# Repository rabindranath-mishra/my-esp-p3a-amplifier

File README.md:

# My ESP P3A Amplifier Build (Y2026)

I have been making my own audio equipment since I was a teenager. I firmly believe that if you understand electronics, it is far better to build your own gear. You can craft something of exceptionally high quality, tailored precisely to your personal taste, and at a fraction of the cost of a mediocre commercial unit. For that matter, I build anything that I feel is not worth the retail price tag for its given quality—particularly in the domains of computers, electronics, and anything that can be 3D printed. Fortunately, all three are lifelong hobbies of mine.

Back in 2013–14, I built a stereo power amplifier for my home. My commercial home theater system (a mediocre setup received as a wedding gift) had given up the ghost, and repairing it was neither economical nor satisfying. I was unwilling to shell out exorbitant sums for high-end retail audio gear. After deep research across the DIY audio community, I chose to build a design by one of my greatest inspirations, Rod Elliott (Elliott Sound Products): the legendary [ESP Project 3A (P3A)](https://www.sound-au.com/project3a.htm). 

That 2013 amplifier was an absolute workhorse. It sounded magnificent and served faithfully for over a decade without missing a single beat. However, I was never 100% satisfied with the physical build. Back then in Bangalore, sourcing authentic, audiophile-grade components was an uphill battle involving difficult international orders, long customs delays, and DIY chemical etching of single-sided copper clad boards in my garage. The final unit lacked a professional finish and involved several mechanical compromises.

Fast forward to **2026**: I decided it was time to build a worthy successor. After re-evaluating modern DIY open-source topologies—from Class D modules to complex discrete designs—I reached the unmistakable conclusion that the **ESP P3A** is still King. Its Class AB topology is elegant, highly reliable, and delivers sound quality that easily rivals commercial amplifiers costing thousands of dollars. More importantly, the DIY landscape in India has completely transformed: quality passive components, genuine transistors, fast PCB fabrication (such as JLCPCB), and reputable domestic component distributors are now readily available. In 2026, I could finally build this amplifier to absolute perfection, with zero compromises.

---

## System Architecture & The 5 Building Blocks

A truly great power amplifier is not just an amplifier PCB; it is a carefully engineered system where the power supply, soft start, protection, and grounding work together in total harmony. 

This build integrates five core modules:

1. **The Amplifier Stage (ESP P3A)** – Dual-mono Class AB discrete power amplifier based on [Rod Elliott's ESP P3A](https://www.sound-au.com/project3a.htm).
2. **The Power Supply** – Ultra-low-noise linear power supply with a massive 40,000 µF reserve, inspired by Texas Instruments Reference Design [AN-1849: An Audio Amplifier Power Supply Design](https://www.ti.com/lit/an/snaa057c/snaa057c.pdf).
3. **The Soft Start Circuit** – Mains inrush limiter with auxiliary DC power, inspired by [ESP Project 39](https://www.sound-au.com/project39.htm).
4. **Speaker Protection & Fast Muting (ESP P33)** – DC offset sensing, turn-on delay, and instantaneous AC-loss drop-out based on [ESP Project 33](https://www.sound-au.com/project33.htm).
5. **The Ground Loop Breaker** – Safety earthing and hum-elimination network based on [Rod Elliott's Earthing Guide](https://www.sound-au.com/earthing.htm).

While planning the PCB layouts, I discovered that [gabriel-gearip](https://github.com/gabriel-gearip) had already produced clean, modular KiCad PCB layouts for both the P3A amplifier and P33 speaker protection boards. Check out his [GitHub repository](https://github.com/gabriel-gearip/p3a-amplifier). I chose to use his Gerber files directly for the P3A and P33 boards. For the **Power Supply** and **Soft Start**, I custom-designed the PCBs in KiCad to fit my chassis layout and ordered them fabricated via JLCPCB. Most components were procured domestically from [Robu.in](https://robu.in) and [Sharvi Electronics](https://sharvielectronics.com), along with trusted specialty suppliers.

---

## 1. The Amplifier: ESP P3A

### The Topology
Rod Elliott's Project 3A is celebrated worldwide for good reason. It is a symmetrical-input, discrete Class AB power amplifier that avoids unnecessary complexity while delivering pristine linearity, wide bandwidth, and unconditional stability into real-world loudspeaker loads.

* **Input Stage**: A balanced differential pair (long-tailed pair) utilizing low-noise **BC546** NPN transistors (Q1, Q2) with emitter degeneration resistors ($1\text{ k}\Omega$). This maximizes open-loop linearity and slew rate while minimizing DC offset.
* **Voltage Amplification Stage (VAS)**: A high-current Class A VAS driven by a **BD140** (Q4). 
* **Bias Servo ($V_{be}$ Multiplier)**: Implemented with **Q9 (BC546)**. Because the P3A uses a **Compound Feedback Pair (CFP / Sziklai pair)** output stage, thermal stability is dictated by the driver transistors rather than the output power transistors. Accordingly, Q9 is thermally coupled directly to driver transistor **Q6 (BD140)**—tied face-to-face with thermal paste—rather than mounted on the main heatsink. Quiescent current adjustment is calibrated via a high-precision **Bourns 3296W** multi-turn potentiometer (RV1).
* **Driver & Output Stage**: High-speed **BD139/BD140** drivers feed a complementary pair of modern high-power audio transistors: the **NJW0281** (NPN) and **NJW0302** (PNP) in rugged TO-3P packages. Rated at 15 A, 250 V, and 150 W with an outstanding $30\text{ MHz}$ gain bandwidth, these ON Semiconductor devices exhibit extraordinary $h_{FE}$ linearity across their entire current swing.
* **Emitter Resistors**: Low-inductance **Bevenbi Audio Grade 0.33 $\Omega$ / 10 W** non-inductive ceramic power resistors ensure rock-solid current sharing and thermal stability.
* **On-Board Protection & Zobel**: Independent **3 A fast-blow DC rail fuses** right on each board protect against short circuits, while an on-board Zobel network ($10\ \Omega + 100\text{ nF}$) prevents high-frequency parasitic oscillation into reactive speaker cables.

### Power Output
Operating from $\pm 35\text{ V}$ DC rails, each mono block produces:
* **~60 W RMS into 8 $\Omega$**
* **~100 W RMS into 4 $\Omega$**

This is the sweet spot for domestic high-fidelity listening, providing ample clean headroom, high damping factor, and effortless dynamics without running into thermal or transformer saturation issues.

---

## 2. The Power Supply

An audio amplifier is fundamentally an active valve that modulates raw DC from its power supply into an audio signal. If the power supply is noisy, under-capacitored, or poorly laid out, even the finest amplifier circuit will sound sluggish, hollow, and noisy.

For this build, I designed a dedicated heavy-duty dual-rail linear supply inspired by Texas Instruments' benchmark application report, [AN-1849: An Audio Amplifier Power Supply Design](https://www.ti.com/lit/an/snaa057c/snaa057c.pdf).

### Key Specifications & Design Highlights:
* **300 VA EI-Core Transformer**: Custom heavy-iron transformer with a $230\text{ V}$ AC primary and a **$25\text{--}0\text{--}25\text{ V}$ AC** center-tapped secondary. Under rectification, this produces clean $\pm 35.3\text{ V}$ DC unloaded, settling to a rock-solid $\pm 34\text{ V}$ to $\pm 35\text{ V}$ under continuous load. Mounted on rubber vibration-damping isolation mounts to eliminate mechanical hum.
* **40,000 µF Total Filter Reservoir**: Four massive **Bevenbi 10,000 µF / 100 V** high-ripple snap-in electrolytic capacitors provide **20,000 µF per rail**. This gargantuan capacitive reserve delivers instantaneous transient current for explosive bass slam and reduces 100 Hz ripple to mere millivolts.
* **KBPC3510 Bridge Rectifier — Chassis-Cooled**: Full-wave rectification is handled by a **KBPC3510** (35 A / 1000 V) bridge rectifier. Rather than mounting it upright on the PCB top with a bulky heatsink, I inverted it onto the **underside of the PCB** so that its bare metal body presses flush against the steel chassis floor. A dab of **thermal paste** between the rectifier body and the chassis floor ensures excellent thermal conduction. The chassis itself acts as a passive heatsink, keeping the PCB top uncluttered and the rectifier running cool even under sustained high-current loads.
* **Dual-Footprint High-Frequency Film Bypassing**: To filter out high-frequency noise and RF hash that large can electrolytics cannot absorb due to internal equivalent series inductance (ESL), premium film capacitors bypass each rail.
* **Diode Snubbers & Safety Bleeders**: High-voltage film snubber capacitors across the bridge rectifier legs suppress diode reverse-recovery ringing, while bleeder resistors safely drain the 40,000 µF filter bank when mains power is switched off.
* **Star Grounding Bus**: Thick, high-current copper star ground traces on the PCB provide clean, low-impedance ground return paths for both amplifier channels, the speaker ground terminals, and the center tap.

*(Need this custom PCB? email me at `rabindranathm@gmail.com`.)*

---

## 3. The Soft Start Circuit

### The Problem
A 300 VA linear transformer coupled with a discharged 40,000 µF capacitor bank represents a dead short circuit at the split-second of turn-on. The instantaneous inrush current can spike to **30 to 50+ Amperes**, which routinely trips household miniature circuit breakers (MCBs), stresses or pits the mains power switch, and degrades rectifier diodes over time.

### The Solution: ESP Project 39 Architecture
Inspired by [ESP Project 39](https://www.sound-au.com/project39.htm), I designed a self-contained soft-start PCB that safely limits inrush current while adding isolated auxiliary power rails.

1. **Inrush Current Limiting**: Three heavy-duty **NTC thermistors** (TH1, TH2, TH3) are placed in series with the AC mains live feed. In their cold state, their combined resistance safely chokes the turn-on inrush current to a gentle few amperes.
2. **Precision Delay & Bypass**: An onboard isolated switch-mode power module (**EASY POWER SO12V51000**, accepting $110\text{--}260\text{ V}$ AC and outputting dual isolated $+12\text{ V}$ and $+5\text{ V}$ DC at 1 A) powers an RC timing circuit. After a controlled delay of approximately **100 to 300 mill seconds** (adjustable via an onboard 100 k $\Omega$ trimpot), transistor Q1 turns on and energizes a heavy-duty **SUN HOLD RAS-1215 15 A relay**. The relay contacts short out the NTC thermistors, delivering 100% unimpeded AC mains to the main transformer.
3. **Auxiliary Dual DC Power (+12V & +5V)**: Generating isolated low-voltage DC directly on the soft-start board provides two versatile auxiliary rails:
   * **$+12\text{ V}$ DC**: Powers the **dual chassis exhaust fans** and the **illuminated front-panel power switch LED halo ring**, keeping fan motor commutation hash completely isolated from the sensitive audio rails.
   * **$+5\text{ V}$ DC**: A dedicated clean 5V rail that can be used to power internal or add-on **Bluetooth audio receiver modules** (such as CSR8675, PCM5102, or QCC series boards) or USB DACs without requiring an extra wall wart or inducing digital ground hum into the analog signal path!

*(Need this custom PCB? email me at `rabindranathm@gmail.com`.)*

---

## 4. The Speaker Protection and Muting: ESP P33

High-end loudspeakers are a substantial investment. Because direct-coupled solid-state amplifiers like the P3A do not have output transformers or DC-blocking capacitors, a catastrophic failure of an output transistor would immediately dump the full $\pm 35\text{ V}$ DC rail across your loudspeaker's voice coil, burning it to a crisp in fractions of a second.

To safeguard against this, I incorporated [ESP Project 33](https://www.sound-au.com/project33.htm), built on Gabriel Gearip's PCB layout. This circuit provides three critical protective functions:

### 1. Turn-On Delay (Anti-Thump)
When power is applied, the output relays (**SUN HOLD RAS-1215 15 A**) remain open for **3 to 5 seconds**. This allows the power supply rails to stabilize and DC operating points to settle into equilibrium before the speakers are engaged, ensuring complete silence at turn-on without any annoying "thump" or pop.

### 2. Fast DC Offset Fault Detection
Audio signals are AC; continuous DC should never reach a speaker. The output of both amplifier channels is monitored via a balanced RC low-pass filter (C1, C2 and 100 k$\Omega$ resistors). If either a positive or negative DC offset exceeding $\sim 1.5\text{ V}$ is detected on either channel (caused by component failure or severe overdrive), the sensing transistors trigger instantaneously, de-energizing the relays and disconnecting the speakers in milliseconds.

### 3. Fast Loss-of-AC Power-Off Muting
A dedicated detection input monitors the raw AC line from the transformer secondary. The instant you flip the mains switch to OFF, the incoming AC sine wave vanishes within one half-cycle ($\sim 10\text{--}20\text{ ms}$). The circuit detects this AC loss immediately and drops the speaker relays before the massive 40,000 µF filter capacitors have a chance to slowly drain down. This completely eliminates the squeaks, thumps, or distorted distortion bursts typical of powering off an un-muted amplifier.

---

## 5. The Ground Loop Breaker

Building a truly silent, hum-free audio amplifier requires mastering the art of grounding. 

### The Audiophile Dilemma
* **Electrical Safety**: Mains safety earth (the green/yellow conductor from the IEC inlet) must be securely bolted to the metal chassis. If an internal mains wire ever comes loose or chafes against the metal case, the fault current must trip the home breaker rather than electrifying the chassis and endangering your life.
* **The Ground Loop Problem**: If you directly connect the internal audio signal ground ($0\text{ V}$) to the chassis earth, connecting external audio sources (like a computer, TV, active subwoofer, or DAC) creates a closed loop through the mains safety earth and the audio interconnect shields. Circulating eddy currents induce irritating **50 Hz mains hum** and **100 Hz harmonic buzz** directly into the signal path.

### Rod Elliott's Proven Safety Breaker
Following [Rod Elliott's Earthing Guide](https://www.sound-au.com/earthing.htm), I constructed a dedicated ground-loop isolation bridge bolted directly to the chassis floor:

1. **High-Current Bridge Rectifier (MIC KBPC3510)**: A heavy-duty $35\text{ A} / 1000\text{ V}$ metal-cased bridge rectifier. The two AC terminals are shorted together, and the positive ($+$) and negative ($-$) terminals are shorted together. This forms two pairs of high-current silicon diodes connected in inverse-parallel.
2. **Parallel 10 $\Omega$ / 5 W Ceramic Resistor**: Keeps the internal signal ground referenced near chassis potential while damping any circulating RF currents.
3. **Parallel 100 nF / 400 V Class Film Capacitor**: Shunts radio frequency interference (RFI) and high-frequency EMI noise harmlessly into the chassis shield.

### How It Works in Practice:
* **Under Normal Conditions**: Ground-loop noise voltages are typically tens of millivolts—well below the $\sim 0.7\text{ V}$ conduction threshold of the silicon diodes. The $10\ \Omega$ resistor breaks the low-resistance loop, resulting in a dead-quiet, pitch-black noise floor with zero audible hum at the speaker cones.
* **Under Fault Conditions**: If a catastrophic short occurs (e.g., $230\text{ V}$ mains contacting the audio ground), the voltage immediately exceeds $0.7\text{ V}$. The massive $35\text{ A}$ diodes turn on hard, safely conducting hundreds of amperes of fault current directly into safety earth, instantly blowing the mains fuse before any lethal voltage can appear on external equipment or the chassis.

---

## Optimizations & Field Tweaks

During assembly, testing, and listening sessions, I implemented two crucial optimizations that resolved real-world issues and elevated the amplifier's performance:

### 1. P3A Miller Capacitor (C4): Upgraded to 56 pF Silver Mica
* **The Original Spec**: The default P3A bill of materials specifies a standard $100\text{ pF}$ ceramic disc capacitor for C4 (the Miller compensation capacitor across the VAS transistor BD140).
* **The Issue**: Standard ceramic disc capacitors have significant dielectric absorption and voltage-dependent capacitance variations, which introduce subtle non-linearities in the high-frequency feedback loop. Furthermore, $100\text{ pF}$ provides a very conservative dominant pole that slightly restricts the amplifier's slew rate.
* **The Upgrade**: I replaced C4 with a high-precision **56 pF Silver Mica** capacitor. Silver mica is revered in high-end audio for its ultra-low dielectric loss, extreme thermal stability, and low distortion. Reducing the value to $56\text{ pF}$ safely maintained ample phase margin while noticeably improving slew rate, resulting in airier, more transparent treble, sweeter vocal decay, and an expansive soundstage without any trace of ringing or instability.

### 2. P33 AC Detection Filter Capacitor: Increased from 1 µF to 10 µF
* **The Issue**: When testing the P33 protection circuit on India's $50\text{ Hz}$ AC mains grid, the relays began **chattering and switching intermittently at 50 Hz**! The original design had assumed a $1\text{ µF}$ capacitor on the rectified AC sensing node. At $50\text{ Hz}$ (where the ripple frequency is lower than $60\text{ Hz}$), the voltage valley between rectified peaks dipped below the threshold of the sensing transistor, causing the relay drive to cycle at mains frequency.
* **The Fix**: I changed the AC detection smoothing capacitor from **$1\text{ µF}$ to $10\text{ µF}$**. This smoothed the rectified DC voltage sufficiently to hold the relay driver rock-solid during operation, while still maintaining lightning-fast drop-out ($<50\text{ ms}$) the moment mains power is cut.

---

## Enclosure, Thermal Design & Wiring

A professional amplifier deserves a chassis that matches its electrical performance.

* **Chassis & Aesthetics**: Housed in a rigid steel enclosure with a custom laser-cut aluminum front panel with heavy-duty rack handles. A center-mounted, flush stainless-steel pushbutton switch with a soft LED halo provides a clean, minimalist face. Gold-accented isolation feet decouple the chassis from furniture vibrations.
* **Thermal Management**: The amplifier boards are bolted to a generous finned aluminum heatsink. Two low-RPM, whisper-quiet exhaust fans with chrome wire grilles pull cool air directly through the heatsink fins and exhaust it out the rear panel, keeping operating temperatures barely lukewarm even during long, loud listening sessions.
* **Rear Panel Connectivity**:
  * Standard IEC mains power inlet socket paired with an independent panel-mount chassis fuse holder for primary AC mains protection.
  * Heavy-duty, gold-plated 5-way speaker binding posts accepting bare wire, spades, or banana plugs.
  * Professional **MX 6.35 mm TRS Female Jack Secure Panel Mount** connectors with positive-locking release latches and isolated chassis bushings for rock-solid, professional audio input connections.
  * **Dedicated Pre-Out Jack**: Provided on the rear panel to feed line-level audio out to an active subwoofer in a future 2.1 setup without needing external signal splitters.
* **Wiring Discipline**:
  * Mains AC wiring is kept strictly confined to the far-left side of the chassis.
  * High-current DC power leads (yellow/blue) are tightly bundled, zip-tied, and anchored to the chassis floor.
  * Low-level audio input lines use double-shielded, grounded audio cables routed far away from the transformer and AC mains leads.

---

## Tips, Tricks & Component Selection Guide

Building a high-fidelity amplifier that performs flawlessly for decades requires paying close attention to component types, tolerances, and mechanical assembly. Cutting corners on a 50-cent passive component or neglecting thermal insulation can cause instability, noise, or instant device destruction. 

Here are the hard-won practical guidelines distilled from Rod Elliott's design notes, TI's AN-1849 application report, and my own hands-on build experience:

### 1. Resistor Selection: Where Type & Wattage Matter

Not all resistors are created equal. The operating conditions determine the ideal resistor chemistry:

| Position | Recommended Value / Spec | Resistor Type & Why |
| :--- | :--- | :--- |
| **Small-Signal Audio Path** (R1–R8, feedback network) | 1/4W to 1/2W, 1% tolerance | **Metal Film (MF)**: Metal film resistors generate significantly lower thermal (Johnson) noise and have negligible voltage coefficient compared to carbon film/carbon composition. They keep the amplifier’s noise floor dead silent. |
| **VAS & Pre-Driver Loading** (P3A R9, R10) | 3.3 k$\Omega$, 1/2W to 1W | **Metal Film or Flameproof Metal Oxide**: These resistors continuously drop voltage from the $\pm 35\text{V}$ rails and run warm. Use at least 0.5W or 1W rating to prevent thermal drift and long-term degradation. |
| **Output Emitter Resistors** (P3A R13, R14) | 0.33 $\Omega$, 5W to 10W | **Non-Inductive Ceramic / Metal Oxide**: *Critical!* Standard cheap spiral-wound wirewound resistors introduce parasitic inductance ($L$) at high frequencies. With modern high-speed output transistors like the NJW0281/NJW0302 ($f_T = 30\text{ MHz}$), inductive emitter resistors can trigger ultrasonic ringing or oscillation. Use dedicated low-inductance audio-grade resistors (e.g., Bevenbi Audio Grade 10W non-inductive ceramic). |
| **Zobel Network Resistor** (P3A R15) | 10 $\Omega$, 1/2W to 1W | **Flameproof Metal Oxide / Non-Inductive**: Absorbs high-frequency capacitive energy. Must be flameproof in case of severe high-frequency parasitic oscillation. |
| **Power Dropping Resistors** (P33 R10, R13; PSU bleeders) | Varied (1W to 5W) | **Power Resistors mounted with clearance**: Resistors that drop rail voltage to zener diodes or relays dissipate real heat. **Mount them 1 to 2 mm above the PCB surface** rather than flush against the board to allow air convection and avoid scorching the fiberglass PCB over years of operation. |

---

### 2. Capacitor Selection: Dielectrics & Voltage Ratings

Capacitor dielectric material has a profound effect on audio transparency, frequency response, and circuit reliability:

* **Input DC-Blocking Capacitor (P3A C1 – 4.7 µF)**:
  * **Use**: High-quality **metallized polyester (PET) or metallized polypropylene (PP)** film capacitor (such as WIMA MKS/MKP or Epcos), rated for $50\text{V}$ or $63\text{V}$.
  * **Avoid**: Never use polarized electrolytics or cheap ceramic discs here. Film capacitors eliminate dielectric distortion and preserve deep, articulated bass without phase smear.
* **Miller Compensation Capacitor (P3A C4 – 56 pF to 100 pF)**:
  * **Use**: **Silver Mica** or **C0G / NP0 Ceramic**. Silver mica is the gold standard here due to its ultra-low dielectric absorption, zero voltage coefficient, and extreme temperature stability.
  * **Avoid**: *Never* use Class 2 or 3 generic ceramics (X7R, Z5U, Y5V). Their capacitance shifts wildly with voltage swing, which injects severe non-linear harmonic distortion directly into the amplifier's dominant feedback loop!
* **High-Frequency Compensation (P3A C2, C6 – 100 pF)**:
  * **Use**: High-stability **C0G / NP0 ceramic** or silver mica.
* **Speaker Protection Sensing Capacitors (P33 C1, C2 – 10 µF)**:
  * **Use**: **Non-Polar (Bipolar / NP)** electrolytic capacitors rated at $25\text{V}$ to $50\text{V}$ (or two $22\text{ µF}$ polarized electrolytics wired in series back-to-back, negative-to-negative).
  * **Why**: The DC detection circuit samples bidirectional AC audio signals. A standard polarized electrolytic will be reverse-biased during negative audio peaks, leading to leakage current, distorted sensing, and false relay tripping.
* **Main Filter Reservoir (Power Supply – 10,000 µF / 100V)**:
  * **Use**: High-ripple-current, low-ESR, $105^\circ\text{C}$ snap-in audio-grade electrolytics.
  * **Voltage Margin**: On $\pm 35\text{V}$ rails, using $100\text{V}$ rated capacitors gives massive dielectric margin against surges, lowers ESR, and guarantees decades of maintenance-free service without drying out.
* **High-Frequency RF Bypass Capacitors**:
  * **Use**: $100\text{ nF}$ metallized film capacitors paralleled across the bridge rectifier legs and placed directly at the amplifier board DC inputs. Large can electrolytics have internal equivalent series inductance (ESL) and become ineffective above tens of kilohertz; film bypass capacitors maintain low rail impedance into the multi-megahertz region.

---

### 3. Special Care & Assembly Precautions

Pay meticulous attention to these mechanical and electrical details during assembly:

> [!CAUTION]
> **Heatsink Transistor Insulation (The #1 Killer of DIY Amplifiers)**
> The metal collector tabs of the TO-3P output transistors (**NJW0281** and **NJW0302**) and driver transistors are **electrically hot**—tied directly to the positive and negative power rails!
> * Mount every power transistor using an individual **mica insulator, Kapton washer, or Bergquist Sil-Pad**, along with an insulating shoulder washer for the mounting screw.
> * Apply a very thin, uniform film of high-quality thermal grease (e.g., Arctic MX-4 or silicone heatsink compound) on both sides of mica washers. Avoid excessive paste, which increases thermal resistance.
> * **MANDATORY MULTIMETER CHECK**: Before applying any power, use your digital multimeter in continuity / resistance mode to test between the collector tab / mounting screw of **every single transistor** and the aluminum heatsink. It MUST read **infinite resistance (open circuit)**. Even a microscopic metal swarf or burr puncturing the mica will short the full DC rail to ground, instantly destroying output transistors upon power-up.

> [!IMPORTANT]
> **Thermal Coupling of the Bias Servo ($V_{be}$ Multiplier): Q9 Tied Directly to Driver Q6**
> One of the most elegant design choices in Rod Elliott's P3A is the use of a **Compound Feedback Pair (CFP / Sziklai pair)** output stage:
> * Unlike standard Darlington (Emitter Follower) amplifiers where the bias transistor must be bolted to the main heatsink, a CFP output stage has 100% local negative feedback around each driver/output pair. As a result, the output stage quiescent current is governed by the $V_{be}$ of the **driver transistors**, not the high-power output transistors!
> * Therefore, **Q9 (BC546)** acts as the bias servo ($V_{be}$ multiplier) and is **thermally coupled directly to driver transistor Q6 (BD140)**. In this build—just as Rod Elliott designed—the flat faces of Q9 and Q6 are placed touching face-to-face with a thin film of thermal grease and tied tightly together using a small zip-tie or heatshrink sleeve.
> * **DO NOT mount Q9 on the main heatsink!** Mounting the bias transistor to the main heatsink in a CFP amplifier leads to sluggish, improper thermal tracking. By tying Q9 directly to driver Q6 right on the PCB, Q9 immediately senses any temperature rise in the driver and automatically reduces the bias voltage, preventing thermal runaway and keeping idle current rock-steady across all listening levels.

> [!TIP]
> **Transistor Matching for Minimal DC Offset & Symmetrical Drive**
> * **Input Differential Pair (Q1, Q2 - BC546B)**: Take 10 to 15 pieces of low-cost BC546B transistors and measure their DC current gain ($h_{FE}$) using a multimeter transistor tester. Select two matched pairs whose $h_{FE}$ values are within **5% to 10%** of each other (one pair for the Left channel, one pair for the Right channel). Symmetrical matching of the input pair ensures the amplifier's DC output offset stays well under **$15\text{ mV}$** at all times, without requiring a DC offset potentiometer or an active DC servo circuit!
> * **Driver & Power Transistors**: If possible, also hand-match complementary pairs in the driver stage (BD139/BD140) and power output stage (NJW0281/NJW0302) for closely matched $h_{FE}$ between positive and negative halves. This ensures symmetrical slew rates and further minimizes even-order harmonic distortion.

> [!NOTE]
> **Wiring & Routing Discipline**
> * **Twist All AC Conductors**: Tightly twist the $230\text{V}$ AC mains leads (Live and Neutral), as well as the transformer secondary AC pairs ($25\text{--}0\text{--}25\text{V}$). Twisting ensures the magnetic fields generated by the heavy alternating currents cancel each other out, preventing hum induction.
> * **Strict Star Grounding**: Never daisy-chain ground wires from one board to another. Every ground connection—power supply center tap, Left amplifier ground, Right amplifier ground, speaker return terminals, and soft-start ground—must run independently back to the heavy central ground bus on the power supply PCB.
> * **Separate Signal Ground from Power Ground**: Small-signal input ground carries minuscule audio currents (microamps), whereas the power ground handles massive speaker return currents (several amps). To prevent heavy speaker currents and supply ripple from modulating the input reference, maintain strict separation between clean signal ground and dirty power ground, tying them together only at the central star point.
> * **Route Small-Signal Lines Away from AC**: Keep low-level shielded audio input cables on the opposite side of the chassis from the AC mains wiring. Where AC and audio signal wires must cross, ensure they cross at a **$90^\circ$ right angle** to minimize capacitive and inductive crosstalk.

---

## Initial Testing & Biasing Guide

If you are building your own ESP P3A, follow this step-by-step commissioning procedure before connecting your prized speakers:

```mermaid
flowchart LR
    A["1. Dim-Bulb Tester<br/>60W bulb in series with AC mains"] --> B["2. Pre-Set Bias Trimpots<br/>Set RV1 to max resistance"]
    B --> C["3. Power Up & Check DC<br/>Rails ±35V, Offset < 15mV"]
    C --> D["4. Warm Up & Adjust Bias<br/>33mV across R13/R14 (~100mA)"]
    D --> E["5. Verify P33 Protection<br/>Turn-on delay & fast AC-drop"]
```

1. **Use a Dim-Bulb Tester**: On initial power-up, wire a $60\text{ W}$ or $100\text{ W}$ incandescent light bulb in series with the AC mains live wire. If there is a short or soldering bridge, the bulb will glow brightly and protect your output transistors from instant destruction. If all is well, the bulb will flare briefly (as the filter caps charge) and then dim to a faint orange glow.
2. **Pre-Set the Bias Trimpots**: Before applying power, turn the **RV1** multiturn trimpot on both amplifier boards to its **maximum resistance**. This ensures the amplifier turns on with minimum quiescent current (zero bias).
3. **Verify DC Offset**: With no input signal and no speakers connected, measure the DC voltage across the speaker output terminals. It should read under $\pm 20\text{ mV}$ (typically $5\text{--}15\text{ mV}$). A offset of < $\pm 100\text{ mV}$ is also fine.
4. **Set Quiescent Bias Current**:
   * Remove the dim-bulb tester and plug directly into mains.
   * Allow the amplifier to idle for 10 minutes to reach operating temperature.
   * Connect a digital multimeter (set to millivolts DC) across one of the $0.33\ \Omega$ emitter resistors (**R13** or **R14**).
   * Slowly rotate trimpot **RV1** until the multimeter reads **$33\text{ mV}$**.
   * By Ohm's Law:
     $$I_{bias} = \frac{V}{R} = \frac{33\text{ mV}}{0.33\ \Omega} = 100\text{ mA}$$
   * A bias current of $100\text{ mA}$ per channel provides ideal Class AB linearity, eliminating crossover distortion while keeping idle dissipation conservative.
   * Re-check the voltage after 30 minutes of warmup and make fine adjustments if necessary.
5. **Verify P33 Operation**:
   * Listen for the crisp click of the P33 speaker relays approximately 3 to 4 seconds after power-on.
   * Power down the amplifier: the relays must click open instantly without the slightest lag, confirming that the AC-loss muting is functioning properly.

---

## Parts Sourcing & PCB Availability

Building an audiophile-grade amplifier in India is now completely viable with local resources:

| Component Category | Recommended Sources | Notes |
| :--- | :--- | :--- |
| **P3A & P33 PCBs** | [gabriel-gearip GitHub](https://github.com/gabriel-gearip/p3a-amplifier) | Download Gerbers & order from JLCPCB |
| **Power Supply PCB** | Contact author (`rabindranathm@gmail.com`) | Custom KiCad layout, JLCPCB 2-layer |
| **Soft Start PCB** | Contact author (`rabindranathm@gmail.com`) | Custom KiCad layout, JLCPCB 2-layer |
| **Passives & Relays** | [Robu.in](https://robu.in), [Sharvi Electronics](https://sharvielectronics.com) | Metal film 1% resistors, Bourns trimmers, Finder/Sun Hold relays |
| **Filter Capacitors** | Bevenbi Audio Grade (10,000 µF / 100 V) | diyaudiocart.com |
| **Transistors** | Robu.in, MV Collection | Authentic ON Semi NJW0281/NJW0302, BD139/140, BC546 |
| **Transformer** | Local transformer winder (Bangalore) | 300 VA EI core, $230\text{ V}$ primary, $25\text{--}0\text{--}25\text{ V}$ secondary |
| **Hardware & Chassis** | 17.5" 2U Cabinet, MV Collection | Finned aluminum heatsink, MX 6.35 mm TRS locking jacks, gold binding posts |

---

## Conclusion & Listening Impressions

Rebuilding the ESP P3A in 2026 was one of the most rewarding audio projects I have undertaken. Seeing the amplifier take shape—from clean KiCad layouts and freshly etched JLCPCB boards to a gleaming, professionally wired chassis—has been immensely satisfying.

How does it sound? Great!; clean, warm, musical, dynamic. 

The combination of the stiff 300 VA transformer and 40,000 µF filter reserve gives the amplifier unflinching grip over the woofer cones. Low-frequency bass notes are fast, punchy, and deeply textured with zero muddiness. The midrange is transparent and organic, rendering acoustic instruments and vocals with uncanny realism. And thanks to the 56 pF Silver Mica Miller capacitor upgrade, the highs are smooth, airy, and fatigue-free even during multi-hour listening sessions. Most impressively, the ground loop breaker and star ground layout ensure the background is pitch black, a very faint trace of hiss or can be heard with your ear pressed directly against the tweeter though, but virtually inaudible from distance.

If you have been contemplating building your own high-fidelity amplifier, look no further than the ESP P3A. It is a timeless masterpiece of audio engineering that will reward you with decades of musical joy.

Happy building!

---
*Created by Rabindranath Mishra.*  
*If you have questions about the build, need the custom Power Supply or Soft Start Gerbers, or want component tips, feel free to open an issue or reach out at `rabindranathm@gmail.com`.*

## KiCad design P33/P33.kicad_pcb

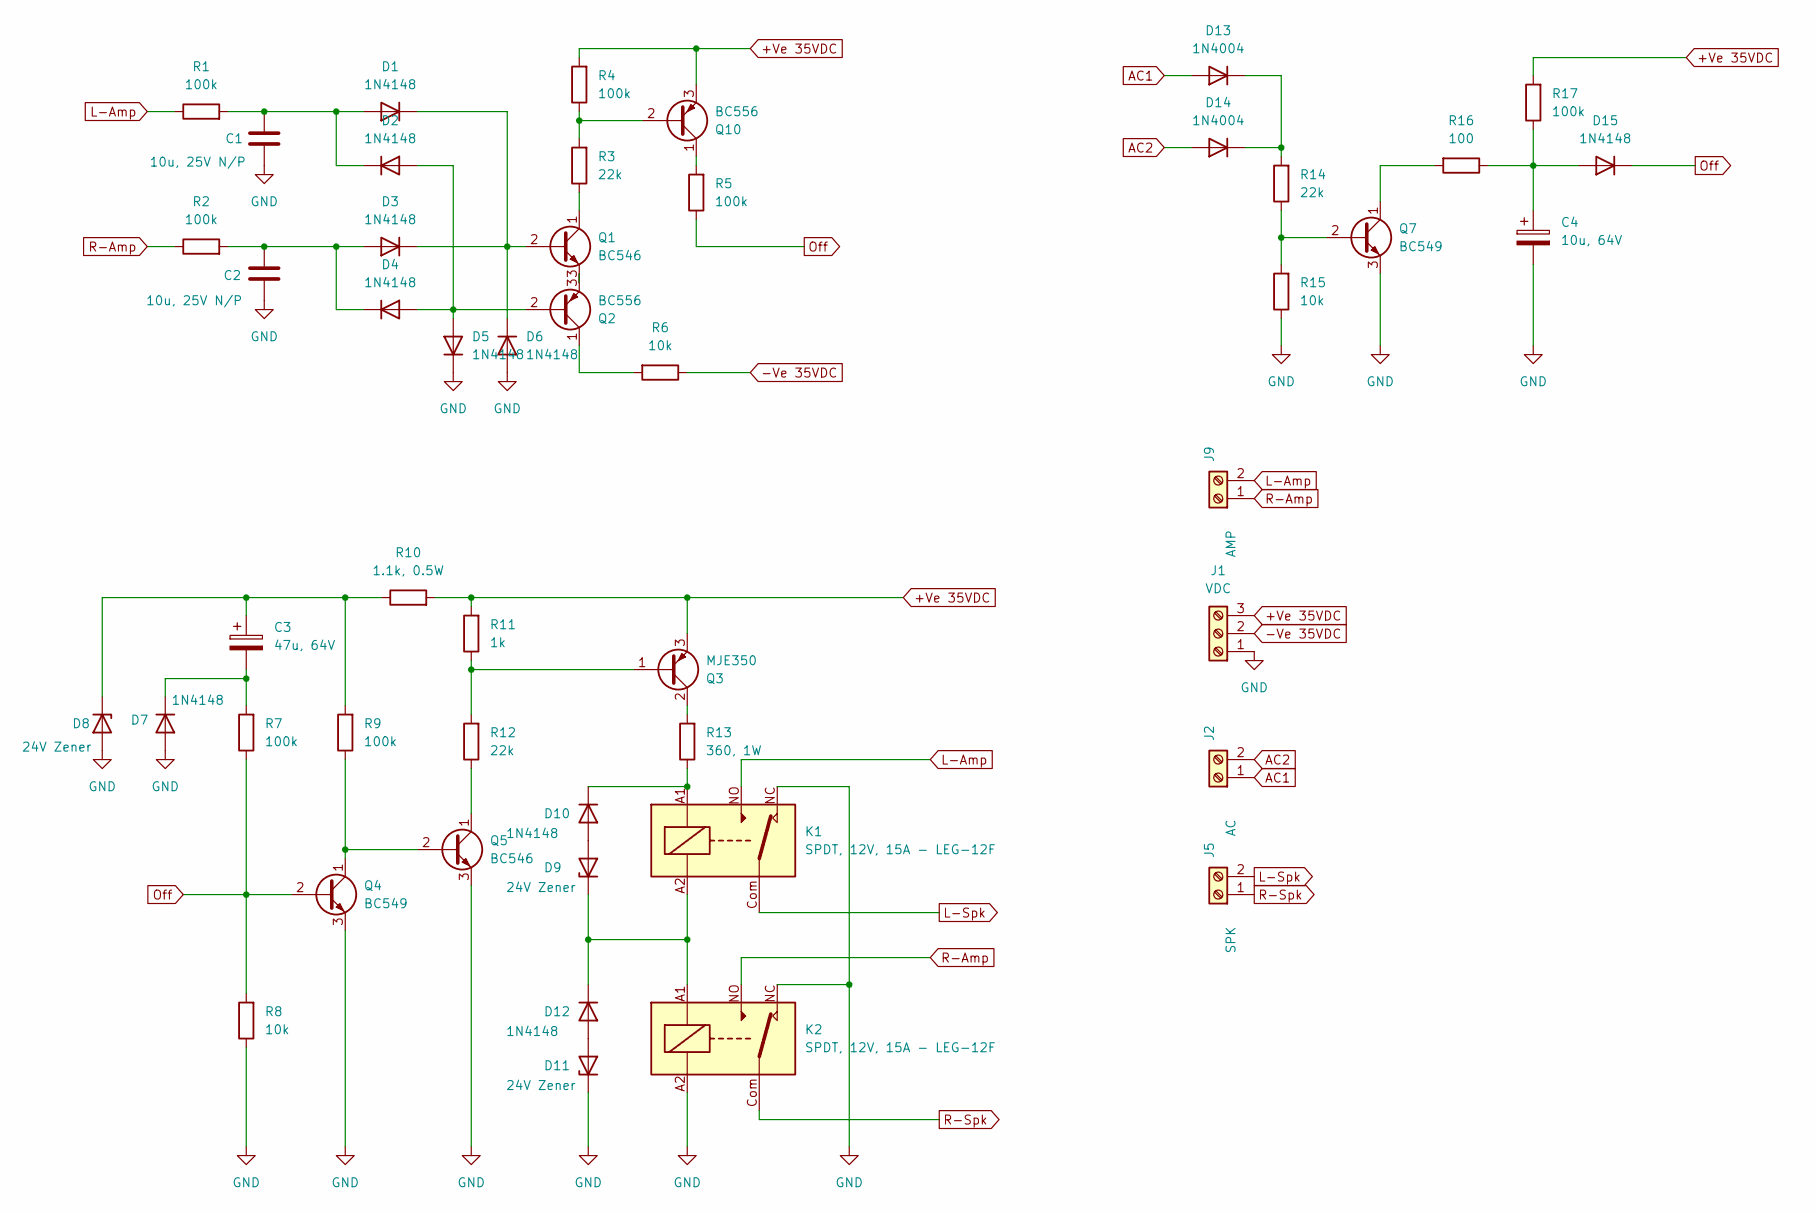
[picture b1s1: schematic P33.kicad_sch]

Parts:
C1, C2: 10u, 25V N/P; R_Axial_DIN0922_L20.0mm_D9.0mm_P7.62mm_Vertical
C3: 47u, 64V; CP_Radial_D6.3mm_P2.50mm
C4: 10u, 64V; CP_Radial_D5.0mm_P2.50mm
D1, D2, D3, D4, D5, D6, D7, D10, D12, D15: 1N4148; D_DO-34_SOD68_P7.62mm_Horizontal
D8, D9, D11: 24V Zener; D_DO-41_SOD81_P10.16mm_Horizontal
D13, D14: 1N4004; D_DO-41_SOD81_P10.16mm_Horizontal
J1: VDC; Conector_Verde_3_pini
J2: AC; Conector_Verde_2_pini
J5: SPK; Conector_Verde_2_pini
J9: AMP; Conector_Verde_2_pini
K1, K2: SPDT, 12V, 15A - LEG-12F; Relay_SPDT_Finder_36.11
Q1, Q5: BC546; TO-92_Inline_Wide
Q2, Q10: BC556; TO-92_Inline_Wide
Q3: MJE350
Q4, Q7: BC549; TO-92_Inline_Wide
R1, R2, R4, R5, R7, R9, R17: 100k; R_Axial_DIN0207_L6.3mm_D2.5mm_P10.16mm_Horizontal
R3, R12, R14: 22k; R_Axial_DIN0207_L6.3mm_D2.5mm_P10.16mm_Horizontal
R6, R8, R15: 10k; R_Axial_DIN0207_L6.3mm_D2.5mm_P10.16mm_Horizontal
R10: 1.1k, 0.5W; R_Axial_DIN0207_L6.3mm_D2.5mm_P10.16mm_Horizontal
R11: 1k; R_Axial_DIN0207_L6.3mm_D2.5mm_P10.16mm_Horizontal
R13: 360, 1W; R_Axial_DIN0411_L9.9mm_D3.6mm_P15.24mm_Horizontal
R16: 100; R_Axial_DIN0207_L6.3mm_D2.5mm_P10.16mm_Horizontal

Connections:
+Ve 35VDC: J1.3, Q3.3 (E), Q10.3 (E), R4.2, R10.2, R11.2, R17.2
-Ve 35VDC: J1.2, R6.1
AC1: D13.2 (A), J2.1
AC2: D14.2 (A), J2.2
GND: C1.2, C2.2, C4.2, D5.1 (K), D6.2 (A), D7.2 (A), D8.2 (A), D11.1 (K), J1.1, K1.NC, K2.A2, K2.NC, Q4.3 (E), Q5.3 (E), Q7.3 (E), R8.1, R15.1
L-Amp: J9.2, K1.NO, R1.1
L-Spk: J5.2, K1.Com
unnamed: C1.1, D1.2 (A), D2.1 (K), R1.2
unnamed: D1.1 (K), D3.1 (K), D6.1 (K), Q1.2 (B)
unnamed: D2.2 (A), D4.2 (A), D5.2 (A), Q2.2 (B)
unnamed: C2.1, D3.2 (A), D4.1 (K), R2.2
unnamed: C3.2, D7.1 (K), R7.2
unnamed: C3.1, D8.1 (K), R9.2, R10.1
unnamed: D9.2 (A), D10.2 (A)
unnamed: D10.1 (K), K1.A1, R13.1
unnamed: D11.2 (A), D12.2 (A)
unnamed: D9.1 (K), D12.1 (K), K1.A2, K2.A1
unnamed: D13.1 (K), D14.1 (K), R14.2
unnamed: C4.1, D15.2 (A), R16.1, R17.1
unnamed: Q1.1 (C), R3.1
unnamed: Q1.3 (E), Q2.3 (E)
unnamed: Q2.1 (C), R6.2
unnamed: Q3.1 (B), R11.1, R12.2
unnamed: Q3.2 (C), R13.2
unnamed: Q4.1 (C), Q5.2 (B), R9.1
unnamed: Q5.1 (C), R12.1
unnamed: Q7.2 (B), R14.1, R15.2
unnamed: Q7.1 (C), R16.2
unnamed: Q10.2 (B), R3.2, R4.1
unnamed: Q10.1 (C), R5.2
Off: D15.1 (K), Q4.2 (B), R5.1, R7.1, R8.2
R-Amp: J9.1, K2.NO, R2.1
R-Spk: J5.1, K2.Com

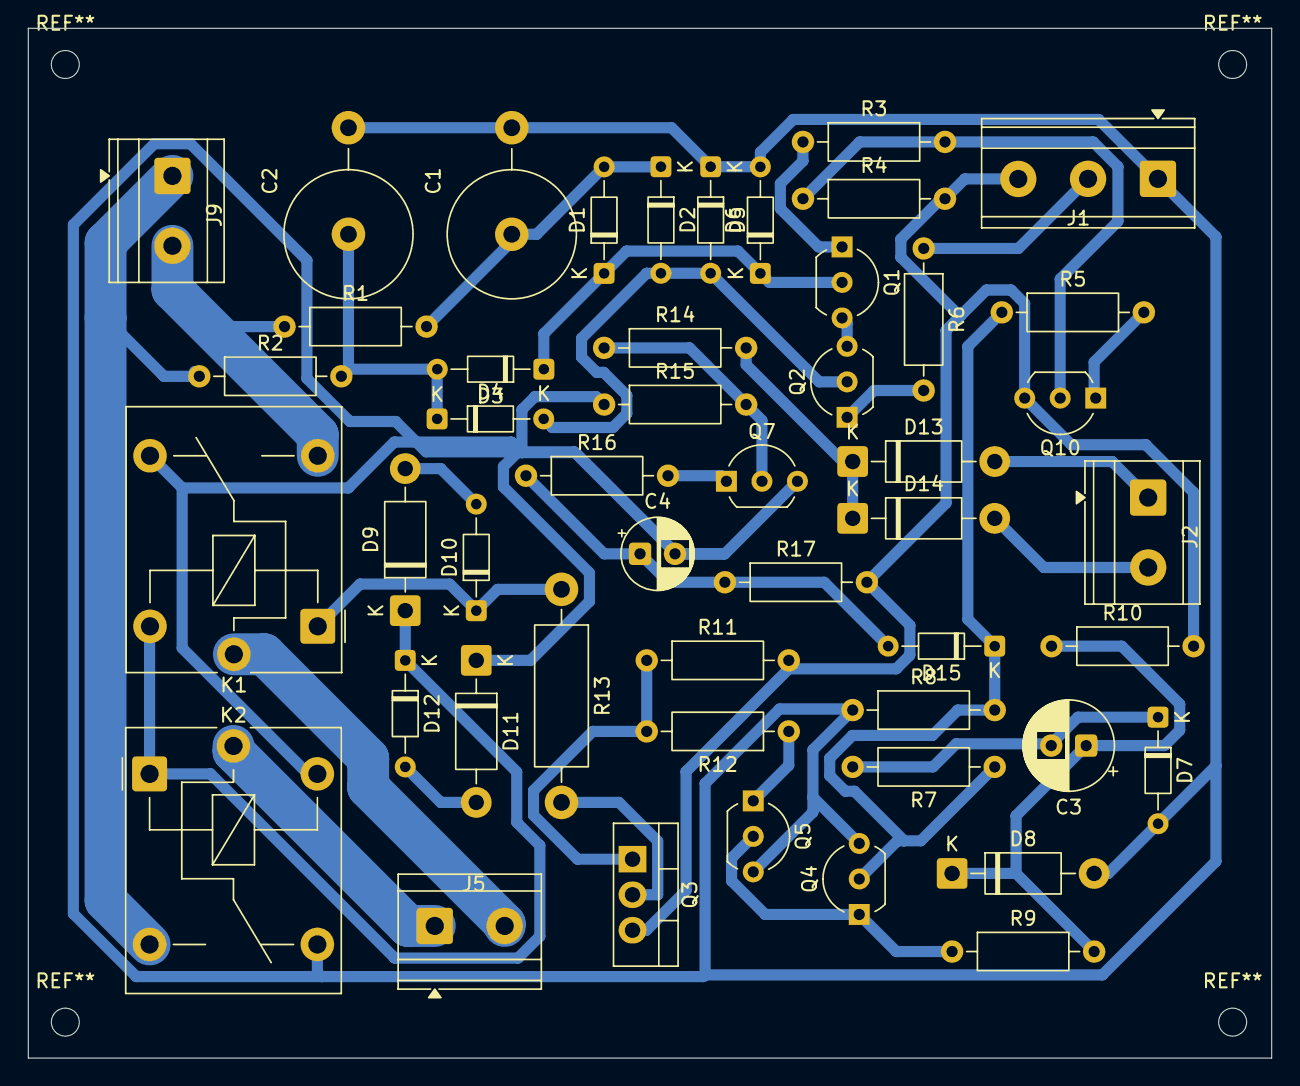
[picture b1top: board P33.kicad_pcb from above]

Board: 2 copper layers, 88.9 x 73.7 mm, 49 parts (0 on the bottom side), 33 nets.

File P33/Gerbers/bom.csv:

Designator,Footprint,Quantity,Value,LCSC Part #
"C1, C2",R_Axial_DIN0922_L20.0mm_D9.0mm_P7.62mm_Vertical,2,"10u, 25V N/P",
C3,CP_Radial_D6.3mm_P2.50mm,1,"47u, 64V",
C4,CP_Radial_D5.0mm_P2.50mm,1,"10u, 64V",
"D1, D10, D12, D15, D2, D3, D4, D5, D6, D7",D_DO-34_SOD68_P7.62mm_Horizontal,10,1N4148,
"D11, D8, D9",D_DO-41_SOD81_P10.16mm_Horizontal,3,24V Zener,
"D13, D14",D_DO-41_SOD81_P10.16mm_Horizontal,2,1N4004,
J1,Conector_Verde_3_pini,1,VDC,
J2,Conector_Verde_2_pini,1,AC,
J5,Conector_Verde_2_pini,1,SPK,
J9,Conector_Verde_2_pini,1,AMP,
"K1, K2",Relay_SPDT_Finder_36.11,2,"SPDT, 12V, 15A - LEG-12F",
"Q1, Q5",TO-92_Inline_Wide,2,BC546,
"Q10, Q2",TO-92_Inline_Wide,2,BC556,
Q3,MJE350,1,MJE350,
"Q4, Q7",TO-92_Inline_Wide,2,BC549,
"R1, R17, R2, R4, R5, R7, R9",R_Axial_DIN0207_L6.3mm_D2.5mm_P10.16mm_Horizontal,7,100k,
R10,R_Axial_DIN0207_L6.3mm_D2.5mm_P10.16mm_Horizontal,1,"1.1k, 0.5W",
R11,R_Axial_DIN0207_L6.3mm_D2.5mm_P10.16mm_Horizontal,1,1k,
"R12, R14, R3",R_Axial_DIN0207_L6.3mm_D2.5mm_P10.16mm_Horizontal,3,22k,
R13,R_Axial_DIN0411_L9.9mm_D3.6mm_P15.24mm_Horizontal,1,"360, 1W",
"R15, R6, R8",R_Axial_DIN0207_L6.3mm_D2.5mm_P10.16mm_Horizontal,3,10k,
R16,R_Axial_DIN0207_L6.3mm_D2.5mm_P10.16mm_Horizontal,1,100,

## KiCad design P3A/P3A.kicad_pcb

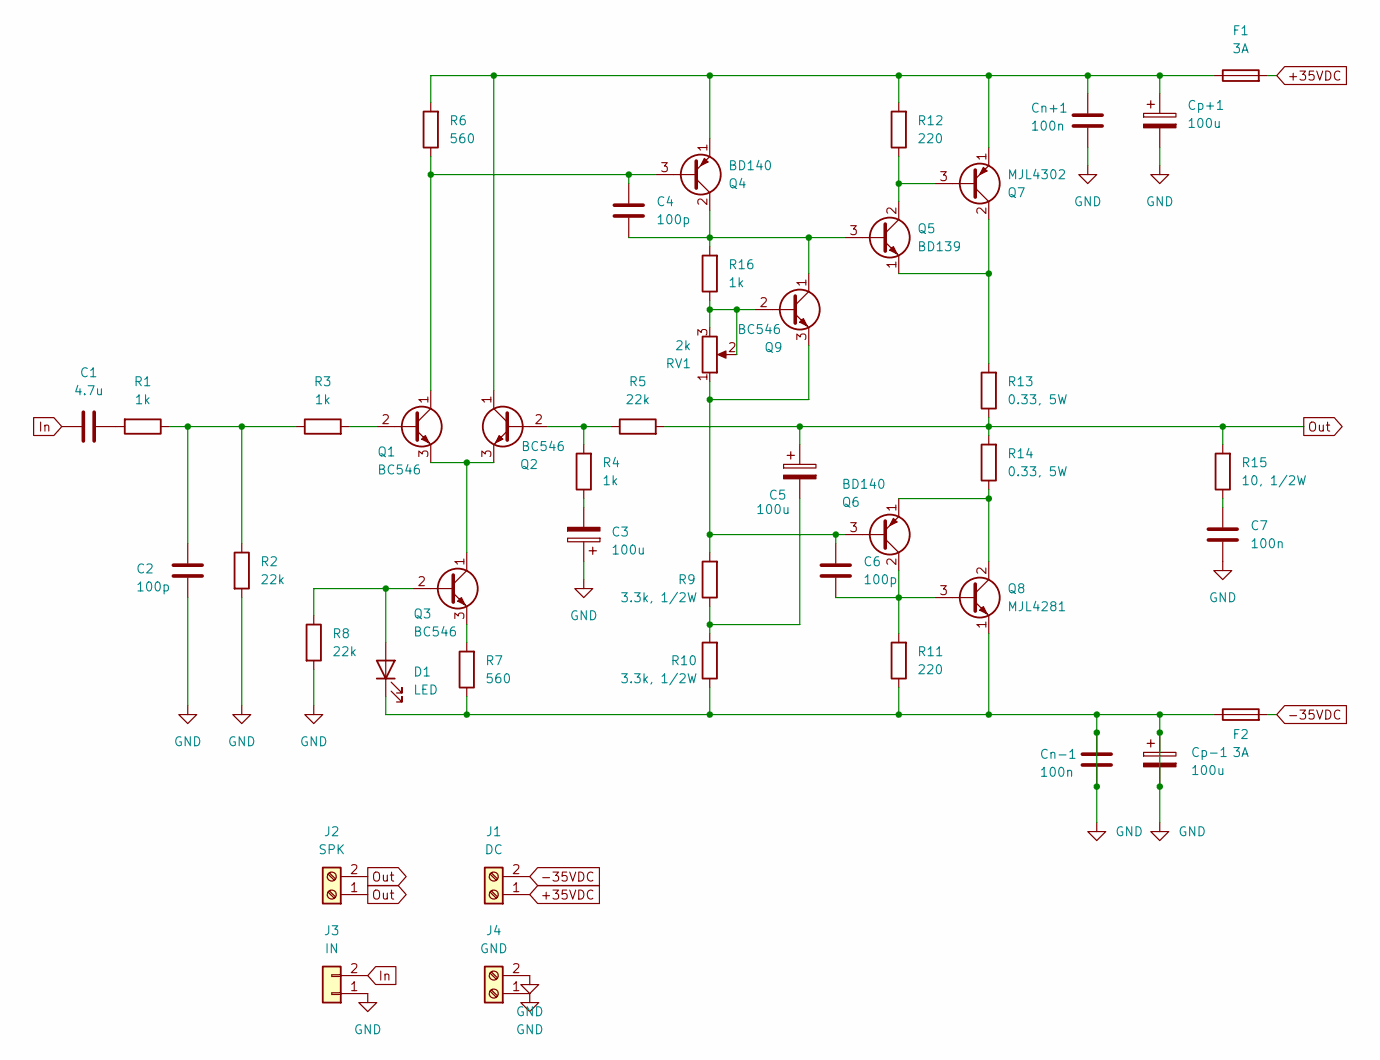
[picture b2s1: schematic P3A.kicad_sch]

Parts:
C1: 4.7u; C_Rect_L18.0mm_W7.0mm_P15.00mm_FKS3_FKP3
C2, C4, C6: 100p; C_Disc_D4.3mm_W1.9mm_P5.00mm
C3, C5: 100u; CP_Radial_D8.0mm_P3.50mm
C7: 100n; C_Rect_L7.2mm_W2.5mm_P5.00mm
Cn+1: 100n; C_Rect_L7.2mm_W2.5mm_P5.00mm
Cn-1: 100n; C_Rect_L7.2mm_W2.5mm_P5.00mm
Cp+1: 100u; CP_Radial_D8.0mm_P3.50mm
Cp-1: 100u; CP_Radial_D8.0mm_P3.50mm
D1: LED; LED_D3.0mm
F1, F2: 3A; Fuseholder_Clip-5x20mm_Littelfuse_445-030_Inline_P20.50x5.2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
J1: DC; Conector_Verde_2_pini
J2: SPK; Conector_Verde_2_pini
J3: IN; JST_XH_B2B-XH-A_1x02_P2.50mm_Vertical
J4: GND; Conector_Verde_2_pini
Q1, Q2, Q3, Q9: BC546; TO-92_Inline_Wide
Q4, Q6: BD140; TO-126-3_Vertical
Q5: BD139; TO-126-3_Vertical
Q7: MJL4302; TO-264-3_Horizontal_TabUp
Q8: MJL4281; TO-264-3_Horizontal_TabUp
R1, R3, R4, R16: 1k; R_Axial_DIN0207_L6.3mm_D2.5mm_P10.16mm_Horizontal
R2, R5, R8: 22k; R_Axial_DIN0207_L6.3mm_D2.5mm_P10.16mm_Horizontal
R6, R7: 560; R_Axial_DIN0207_L6.3mm_D2.5mm_P10.16mm_Horizontal
R9, R10: 3.3k, 1/2W; R_Axial_DIN0309_L9.0mm_D3.2mm_P12.70mm_Horizontal
R11, R12: 220; R_Axial_DIN0207_L6.3mm_D2.5mm_P10.16mm_Horizontal
R13, R14: 0.33, 5W; R_Axial_Power_L25.0mm_W9.0mm_P27.94mm
R15: 10, 1/2W; R_Axial_DIN0309_L9.0mm_D3.2mm_P12.70mm_Horizontal
RV1: 2k; Potentiometer_Bourns_3296W_Vertical

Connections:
+35VDC: F1.2, J1.1
-35VDC: F2.2, J1.2
In: C1.1, J3.2
unnamed: C1.2, R1.2
unnamed: C2.2, R1.1, R2.1, R3.1
unnamed: C3.2, R4.1
unnamed: C5.2, R9.1, R10.2
unnamed: C7.1, R15.1
unnamed: D1.2 (A), Q3.2 (B), R8.1
unnamed: Q1.2 (B), R3.2
unnamed: C4.1, Q1.1 (C), Q4.3 (B), R6.1
unnamed: Q1.3 (E), Q2.3 (E), Q3.1 (C)
unnamed: Q2.2 (B), R4.2, R5.1
unnamed: Cn+1.1, Cp+1.1, F1.1, Q2.1 (C), Q4.1 (E), Q7.1 (E), R6.2, R12.2
unnamed: Q3.3 (E), R7.2
unnamed: C4.2, Q4.2 (C), Q5.3 (B), Q9.1 (C), R16.2
unnamed: Q5.2 (C), Q7.3 (B), R12.1
unnamed: Q5.1 (E), Q7.2 (C), R13.2
unnamed: C6.1, Q6.3 (B), Q9.3 (E), R9.2, RV1.1
unnamed: C6.2, Q6.2 (C), Q8.3 (B), R11.2
unnamed: Q6.1 (E), Q8.2 (C), R14.1
unnamed: Q9.2 (B), R16.1, RV1.2, RV1.3
Out: C5.1, J2.1, J2.2, R5.2, R13.1, R14.2, R15.2

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
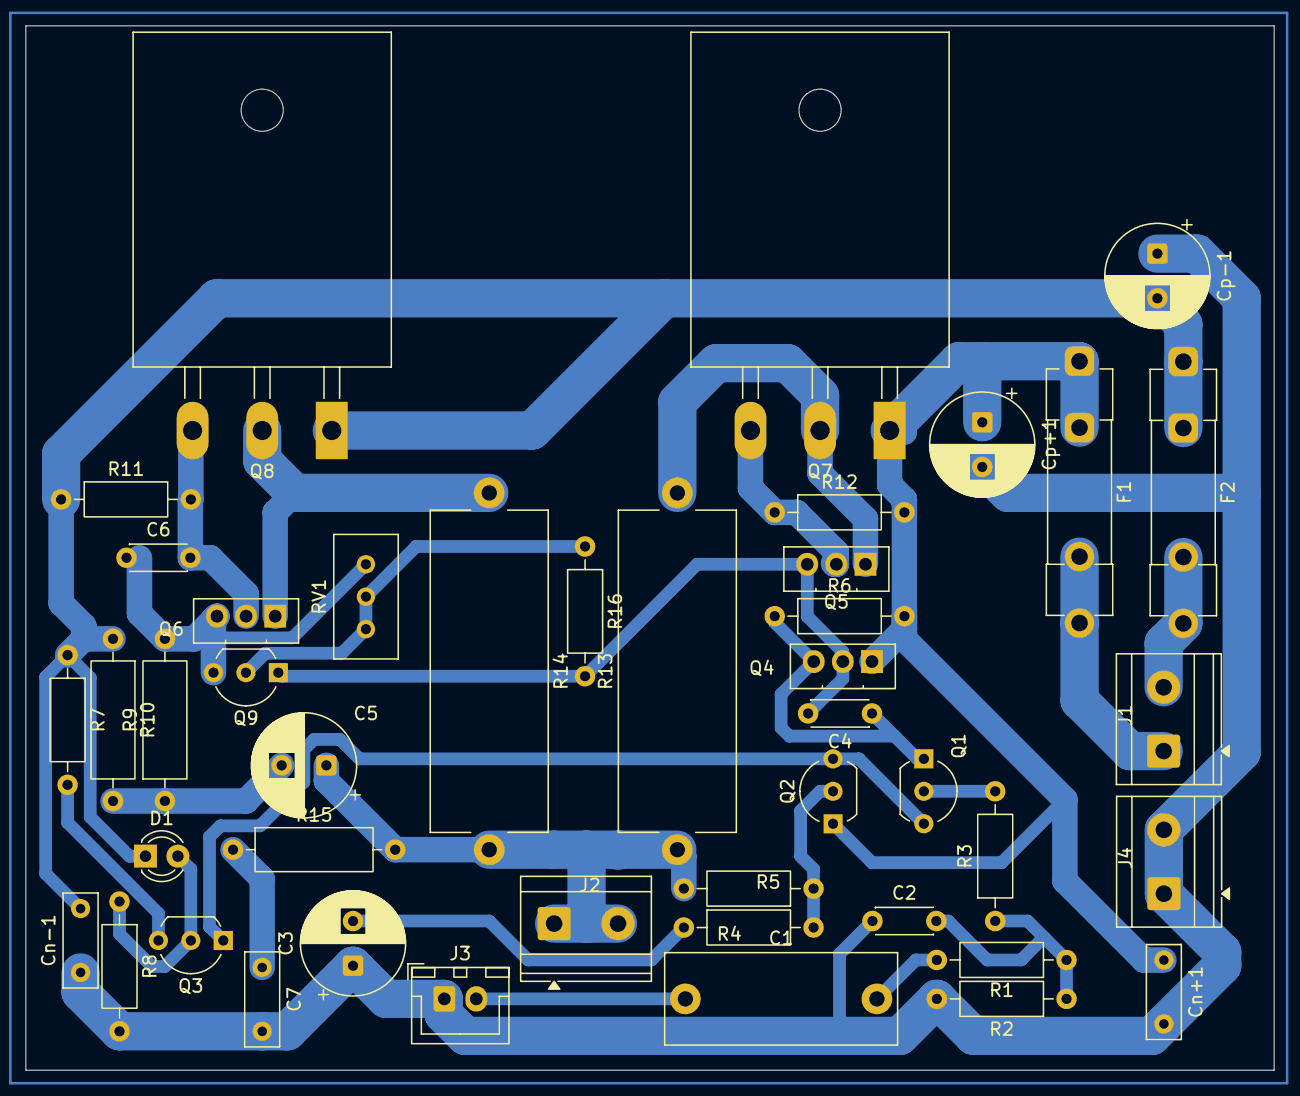
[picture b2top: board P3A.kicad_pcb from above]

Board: 2 copper layers, 97.8 x 81.8 mm, 44 parts (0 on the bottom side), 25 nets.

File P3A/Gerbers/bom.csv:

Designator,Footprint,Quantity,Value,LCSC Part #
C1,C_Rect_L18.0mm_W7.0mm_P15.00mm_FKS3_FKP3,1,4.7u,
"C2, C4, C6",C_Disc_D4.3mm_W1.9mm_P5.00mm,3,100p,
"C3, C5, CP+1, CP-1",CP_Radial_D8.0mm_P3.50mm,4,100u,
"C7, CN+1, CN-1",C_Rect_L7.2mm_W2.5mm_P5.00mm,3,100n,
D1,LED_D3.0mm,1,LED,
"F1, F2",Fuseholder_Clip-5x20mm_Littelfuse_445-030_Inline_P20.50x5.20mm_D1.30mm_Horizontal,2,3A,
J1,Conector_Verde_2_pini,1,DC,
J2,Conector_Verde_2_pini,1,SPK,
J3,JST_XH_B2B-XH-A_1x02_P2.50mm_Vertical,1,IN,
J4,Conector_Verde_2_pini,1,GND,
"Q1, Q2, Q3, Q9",TO-92_Inline_Wide,4,BC546,
"Q4, Q6",TO-126-3_Vertical,2,BD140,
Q5,TO-126-3_Vertical,1,BD139,
Q7,TO-264-3_Horizontal_TabUp,1,MJL4302,
Q8,TO-264-3_Horizontal_TabUp,1,MJL4281,
"R1, R16, R3, R4",R_Axial_DIN0207_L6.3mm_D2.5mm_P10.16mm_Horizontal,4,1k,
"R10, R9",R_Axial_DIN0309_L9.0mm_D3.2mm_P12.70mm_Horizontal,2,"3.3k, 1/2W",
"R11, R12",R_Axial_DIN0207_L6.3mm_D2.5mm_P10.16mm_Horizontal,2,220,
"R13, R14",R_Axial_Power_L25.0mm_W9.0mm_P27.94mm,2,"0.33, 5W",
R15,R_Axial_DIN0309_L9.0mm_D3.2mm_P12.70mm_Horizontal,1,"10, 1/2W",
"R2, R5, R8",R_Axial_DIN0207_L6.3mm_D2.5mm_P10.16mm_Horizontal,3,22k,
"R6, R7",R_Axial_DIN0207_L6.3mm_D2.5mm_P10.16mm_Horizontal,2,560,
RV1,Potentiometer_Bourns_3296W_Vertical,1,2k,
